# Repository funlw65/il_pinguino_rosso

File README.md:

[Go back to the main site](https://funlw65.github.io/)
<hr />

## :boom: Welcome!

This is a PIC alternative to Sanguino board, featuring the PIC18F46K22 microcontroller.

The board is designed in Eagle 7.5.0.

BTW, I'm not interested in any online/cloud based CAD solution/application. If not Eagle, then I will always have a good desktop alternative for my public and personal work and is what I always envagelize.   

```
 Page done.
```

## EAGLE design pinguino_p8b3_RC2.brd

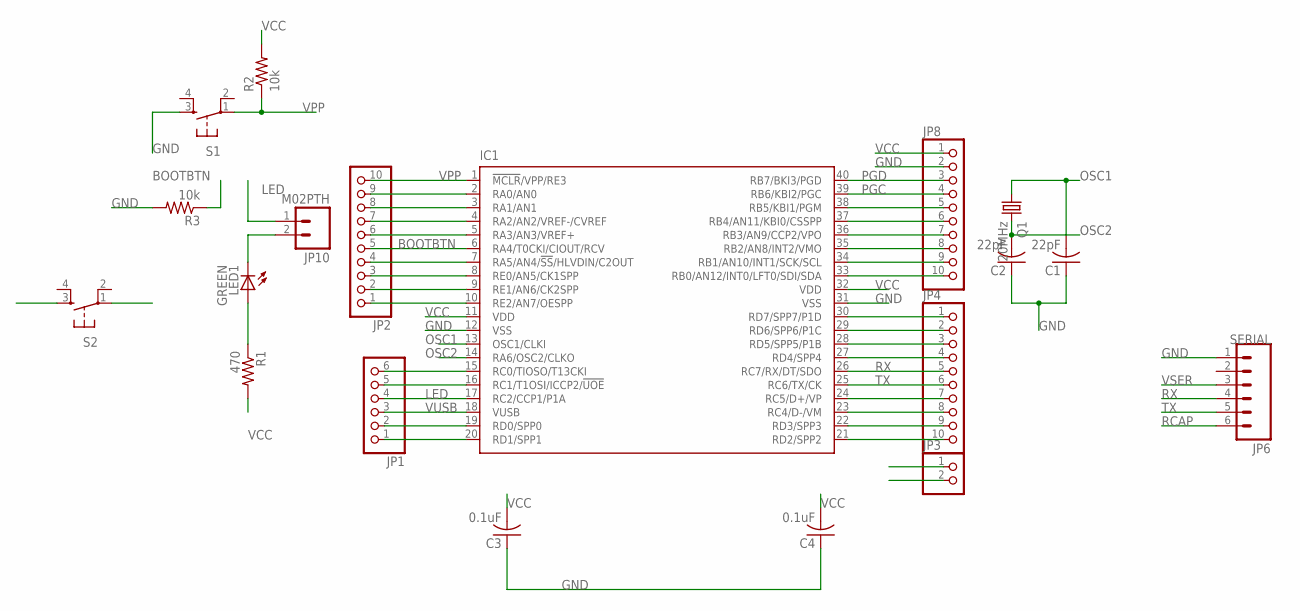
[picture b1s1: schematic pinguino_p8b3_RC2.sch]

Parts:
C1, C2: 22pF; C025-025X050
C3, C4: 0.1uF; C025-025X050
IC1: PIC18F4550_40; DIL40
JP1: PINHD-1X6; 1X06
JP2, JP4, JP8: PINHD-1X10; 1X10
JP3: PINHD-1X2; 1X02
JP6: M06SIP; 1X06
JP10: M02PTH; 1X02
LED1: GREEN; LED3MM
Q1: 20MHz; HC49US
R1: 470; 0207/10
R2, R3: 10k; 0207/7
S1, S2: TAC_SWITCHPTH; TACTILE-PTH

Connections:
BOOTBTN: IC1.6 (RA4/T0CKI/CIOUT/RCV), JP2.5, R3.1, S2.1
GND: C1.1, C2.1, C3.1, C4.1, IC1.12 (VSS), IC1.31 (VSS), JP6.1, JP8.2, R3.2, S1.3
LED: IC1.17 (RC2/CCP1/P1A), JP1.4, JP10.1
unnamed: LED1.A, R1.1
unnamed: JP10.2, LED1.K (C)
unnamed: IC1.38 (RB5/KBI1/PGM), JP8.5
unnamed: IC1.37 (RB4/AN11/KBI0/CSSPP), JP8.6
unnamed: IC1.36 (RB3/AN9/CCP2/VPO), JP8.7
unnamed: IC1.35 (RB2/AN8/INT2/VMO), JP8.8
unnamed: IC1.34 (RB1/AN10/INT1/SCK/SCL), JP8.9
unnamed: IC1.33 (RB0/AN12/INT0/LFT0/SDI/SDA), JP8.10
unnamed: IC1.30 (RD7/SPP7/P1D), JP4.1
unnamed: IC1.29 (RD6/SPP6/P1C), JP4.2
unnamed: IC1.28 (RD5/SPP5/P1B), JP4.3
unnamed: IC1.27 (RD4/SPP4), JP4.4
unnamed: IC1.24 (RC5/D+/VP), JP4.7
unnamed: IC1.23 (RC4/D-/VM), JP4.8
unnamed: IC1.22 (RD3/SPP3), JP4.9
unnamed: IC1.15 (RC0/TIOSO/T13CKI), JP1.6
unnamed: IC1.16 (RC1/T1OSI/ICCP2/!UOE), JP1.5
unnamed: IC1.21 (RD2/SPP2), JP4.10
unnamed: IC1.19 (RD0/SPP0), JP1.2
unnamed: IC1.20 (RD1/SPP1), JP1.1
unnamed: IC1.2 (RA0/AN0), JP2.9
unnamed: IC1.3 (RA1/AN1), JP2.8
unnamed: IC1.4 (RA2/AN2/VREF-/CVREF), JP2.7
unnamed: IC1.5 (RA3/AN3/VREF+), JP2.6
unnamed: IC1.7 (RA5/AN4/!SS!/HLVDIN/C2OUT), JP2.4
unnamed: IC1.8 (RE0/AN5/CK1SPP), JP2.3
unnamed: IC1.9 (RE1/AN6/CK2SPP), JP2.2
unnamed: IC1.10 (RE2/AN7/OESPP), JP2.1
OSC1: C1.2, IC1.13 (OSC1/CLKI), Q1.1
OSC2: C2.2, IC1.14 (RA6/OSC2/CLKO), Q1.2
PGC: IC1.39 (RB6/KBI2/PGC), JP8.4
PGD: IC1.40 (RB7/BKI3/PGD), JP8.3
RCAP: JP6.6
RX: IC1.26 (RC7/RX/DT/SDO), JP4.5, JP6.4
TX: IC1.25 (RC6/TX/CK), JP4.6, JP6.5
VCC: C3.2, C4.2, IC1.11 (VDD), IC1.32 (VDD), JP3.1, JP8.1, R1.2, R2.2, S2.3
VPP: IC1.1 (!MCLR!/VPP/RE3), JP2.10, R2.1, S1.1
VSER: JP3.2, JP6.3
VUSB: IC1.18 (VUSB), JP1.3

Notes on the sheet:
SERIAL

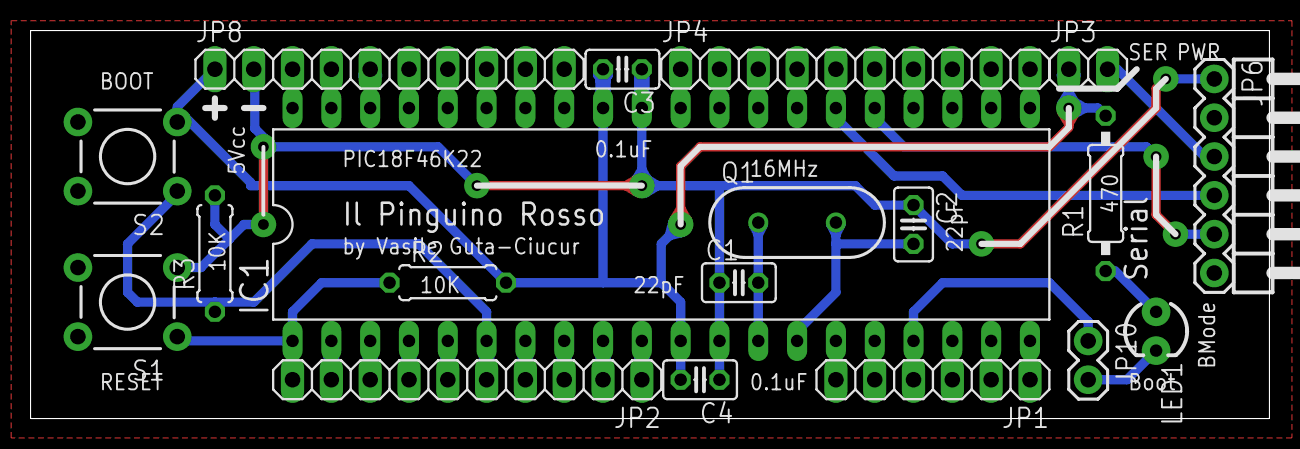
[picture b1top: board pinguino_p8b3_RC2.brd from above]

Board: 2 copper layers, 81.1 x 25.4 mm, 19 parts (0 on the bottom side), 41 nets.

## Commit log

2017-05-22 Set theme jekyll-theme-midnight
2017-05-22 Adding the schematic and pcb
2018-05-08 Update README.md
    detering cloud flies...

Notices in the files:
parts and their libraries:
SparkFun-Electromechanical: Licensing: CC v3.0 Share-Alike You are welcome to use this library for commercial purposes.
